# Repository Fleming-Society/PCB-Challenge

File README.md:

# UCL Fleming x KCL Tech x Oxford Engineering: 2026 PCB Challenge | Sponsored by PCBWay

UCL, KCL and Oxford are proud to present the 2026 PCB Challenge. Many thanks to PCBWay for sponsoring the prizes. 

If you have any questions please email zceepvb@ucl.ac.uk. Please keep in mind you cannot make a submission/be eligible for the prizes if you do not attend any of the universities organising this event. Within the 7 day period this event is being hosted, any university Engineering society is free to reach out to collaborate at this email address. 

All files are meant for KiCAD v10.0, if you have not updated, you probably should. It is a much better version than KiCAD v9.0 (includes dark mode). 

## Overview

This challenge invites participants to implement the given schematic as a fully wired PCB in the smallest possible size. As an added challenge the purpose of the PCB itself is left ambiguous. You are provided a schematic with all component values and connections intact, and a footprint associated with each schematic symbol. The event runs fully online, and all the necessary information can be found in this GitHub. 

I was inspired to create this challenge by a friend, Taylan Arslan, who gave me what was an essentially impossible challenge to get his PCB to fit within a 40mmx40mm constraint. Despite it being impossible, I learned a lot in those two days trying to accomplish this and the end result is a PCB that I am still very proud of. I hope that participants will also share the same feeling of satisfaction that I got, with the added bonus that this one is not impossible since the smallest possible size is to be determined by one of you. 

From my own experience, no matter how much you may like designing PCBs, ultimately it will become a bit repetitive. Thus to make this challenge more interesting; besides the monetary prize; I also decided to make the purpose of the PCB itself a puzzle to be solved.

## The Challenge

1. **Logic Deduction**: deduce the digital logic function implemented by the provided schematic, purely from the schematic itself (no functional description is given). Deducing this will give you bonus points.
2. **PCB Layout**: design a fully wired, single board PCB implementation of that logic, optimised for the smallest possible board area, within the design constraints below.

This challenge will be running for 7 days, **until the midnight of October 19th.**

Make your **submission** here:
https://forms.cloud.microsoft/e/69LKd5ykra

Your challenge submission should be a public GitHub repo. In this repo you just need to include the files we need. Your submission for the logic deduction is in the form itself. 

## Design Constraints

The keep out zone of the ESP32 antenna does not have to cover any PCB area, it can be left hanging off the edge of the PCB. 

### Board & Layer Stack
- Four layer board (F.Cu / B.Cu + 2 inner layers), 1.6 mm standard FR4 thickness.
- Board outline may be any shape, but must be a single contiguous board (no panelisation or multi-board tricks to reduce measured area).
- Management of the 4 layer stack up (e.g. assignment of signal/power/ground to inner layers) is left entirely to the participant; there is no required or predefined ground/power/signal layer assignment. However, you will be penalised for a stack up that would not actually work. 

### Trace & Clearance Rules
- Minimum trace width: 0.15 mm (6 mil).
- Minimum clearance (trace to trace, trace to pad, trace to via): 0.15 mm (6 mil).
- Minimum copper to board edge clearance: 0.3 mm.
- These values should be set as the global minimum in KiCad's Clearance rules so DRC enforces them automatically. We will check the DRC ourselves when judging. 

### Via Rules
- Minimum via drill diameter: 0.3 mm.
- Minimum via annular ring: 0.15 mm (i.e. minimum via pad diameter of approximately 0.6 mm).
- Vias in pads are not permitted.

### Footprint Rules
- Only default KiCad footprints, or footprints explicitly provided as part of the challenge, may be used.
- Footprints must not be modified from the library originals (this will be checked via KiCad's "footprint does not match library" DRC warning; note that editing a local copy of the library will not bypass this check, and manual review may also be used).
- All footprints must have correctly defined courtyard layers (F.CrtYd / B.CrtYd), and courtyards must not overlap between components. This is enforced via KiCad's built in "courtyard overlap" DRC check.
- Traces and vias may not be routed underneath IC footprints (i.e. within the courtyard area of any IC).

### Silkscreen
- Boards do not need to retain fully legible silkscreen labelling. 

### DRC Pass Criteria
- All submitted boards must pass KiCad's Design Rule Checker (Inspect → Design Rules Checker) with **zero unresolved DRC errors**.
- DRC **warnings** (e.g. minor silkscreen clipping) will not disqualify a board, but excessive or careless warnings may count against a board at the routing quality tie break stage.
- A board with unresolved DRC errors is disqualified from the size based ranking regardless of its footprint area.

### Note on High-Speed & Power Rules
The challenge schematic does include a high speed signal paths (a differential pair requiring a continuous reference plane). It does not however have a significant power delivery requirement (e.g. wide power traces, stitching vias). As such, no specific power plane rules are imposed in this iteration. 

## Judging Criteria

1. **Pass/fail gate**: correct logic deduction and a fully wired, DRC clean board (zero errors) under the given constraints. Boards failing either condition are not eligible for prizes.
2. **Primary ranking metric**: smallest board area (bounding box of the board outline), among all boards that pass the gate above.
3. **Tie breaker**: in the event of a tie, judges will assess routing quality and general layout practice (e.g. via count, trace directness, use of ground fill, silkscreen space, DRC warning count) to determine placement.

## Prizes

- **1st place:** £200
- **2nd place:** £100
- **3rd place:** £50

- All participants who submit a valid entry will receive a certificate of participation, a 10$ coupon on orders above 30$ for PCBWay and a PCB ruler from PCBWay. To be classified as a participant you must actually complete the PCB, this meaning that all the connections have been connected with a trace. Auto trace does not count. 

Expect the results to be announced within a week or two from the end date of the challenge.

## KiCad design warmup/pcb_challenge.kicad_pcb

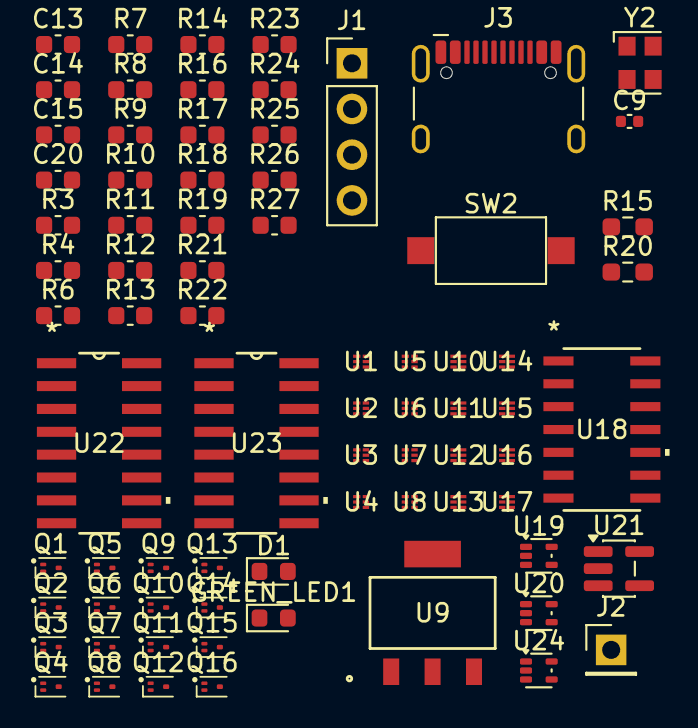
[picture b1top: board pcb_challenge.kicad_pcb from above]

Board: 2 copper layers, 76 parts (0 on the bottom side), 44 nets, no tracks yet.

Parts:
C9: 100nF; C_0402_1005Metric
C13, C14: 1uF; C_0603_1608Metric
C15, C20: 10uF; C_0603_1608Metric
D1: BLED; LED_0603_1608Metric
GREEN_LED1: LED; LED_0603_1608Metric
J1: Conn_01x04_Pin; PinHeader_1x04_P2.54mm_Vertical
J2: Conn_01x01_Pin; PinHeader_1x01_P2.54mm_Vertical
J3: USB_C_Receptacle_HCTL_HC-TYPE-C-16P-01A
Q1, Q2, Q3, Q4, Q5, Q6, Q7, Q8, Q9, Q10, Q11, Q12, Q13, Q14, Q15, Q16: Q_Dual_NPN_PNP_B1E2B2C2E1C1; SOT-1123
R3: 1k; C_0603_1608Metric
R4: 330; C_0603_1608Metric
R6, R24: 1M; C_0603_1608Metric
R7, R8, R9, R10, R11, R12, R13, R14, R16, R17, R18, R19, R21, R22, R23, R25, R26, R27: 10k; C_0603_1608Metric
R15, R20: 5.1k; R_0603_1608Metric_Pad0.98x0.95mm_HandSolder
SW2: SW_MEC_5G; SW_SPST_CK_RS282G05A3
U1, U2, U3, U4, U5, U6, U7, U8, U10, U11, U12, U13, U14, U15, U16, U17: 74AUP1G80; XSON6_SOT1115_NEX
U9: TC1262-25; SOT-223_3MC_MCH
U18: 4068; D14-L
U19, U20, U24: 74LVC1GU04DRL; SOT-553
U21: 74LV1T08GV; SC-74A-5_1.55x2.9mm_P0.95mm
U22, U23: CD74HC283M96; D16
Y2: KC2520Z; Oscillator_SMD_Kyocera_KC2520Z-4Pin_2.5x2.0mm

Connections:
+3.3V: C14.1, R3.1, U1.5 (VCC), U2.5 (VCC), U3.5 (VCC), U4.5 (VCC), U5.5 (VCC), U6.5 (VCC), U7.5 (VCC), U8.5 (VCC), U9.3 (VO), U10.5 (VCC), U11.5 (VCC), U12.5 (VCC), U13.5 (VCC), U14.5 (VCC), U15.5 (VCC), U16.5 (VCC), U17.5 (VCC), U18.14 (Vdd), U19.5 (VCC), U20.5 (VCC), U21.5 (VCC), U22.16 (VCC), U23.16 (VCC), U24.5 (VCC), Y2.4 (VCC)
+5V: C13.1, C15.1, C20.1, GREEN_LED1.2 (A), J3.A4 (VBUS), J3.A9 (VBUS), J3.B4 (VBUS), J3.B9 (VBUS), U9.1 (VI)
CLK: R7.2, U1.2 (C), U2.2 (C), U3.2 (C), U4.2 (C), U5.2 (C), U6.2 (C), U7.2 (C), U8.2 (C), U10.2 (C), U11.2 (C), U12.2 (C), U13.2 (C), U14.2 (C), U15.2 (C), U16.2 (C), U17.2 (C), Y2.3 (CLK)
COUT: U22.9 (COUT), U23.7 (CIN)
D0: U10.4 (~Q), U11.1 (D), U22.6 (B0)
D1: U11.4 (~Q), U12.1 (D), U22.2 (B1)
D2: U12.4 (~Q), U13.1 (D), U22.15 (B2)
D3: U13.4 (~Q), U14.1 (D), U22.11 (B3)
D4: U14.4 (~Q), U15.1 (D), U23.6 (B0)
D5: U15.4 (~Q), U16.1 (D), U23.2 (B1)
D6: U16.4 (~Q), U17.1 (D), U23.15 (B2)
D7: U17.4 (~Q), U23.11 (B3)
EN: J1.1, U21.1 (B), Y2.1 (INH)
F: J2.1 (Pin_1_1), U18.1 (K)
GND: C9.2, C13.2, C14.2, C15.2, C20.2, D1.1 (K), J3.A1 (GND), J3.A12 (GND), J3.B1 (GND), J3.B12 (GND), R4.1, R6.1, R7.1, R8.1, R9.1, R10.1, R11.1, R12.1, R13.1, R14.1, R15.1, R16.1, R17.1, R18.1, R19.1, R20.2, R21.1, R22.1, R23.1, R24.1, R25.1, R26.1, R27.1, SW2.1 (A), SW2.2 (A), U1.3 (GND), U2.3 (GND), U3.3 (GND), U4.3 (GND), U5.3 (GND), U6.3 (GND), U7.3 (GND), U8.3 (GND), U9.2 (GND), U10.3 (GND), U11.3 (GND), U12.3 (GND), U13.3 (GND), U14.3 (GND), U15.3 (GND), U16.3 (GND), U17.3 (GND), U18.7 (Vss), U19.3 (GND), U20.3 (GND), U21.3 (GND), U22.8 (GND), U23.8 (GND), U24.3 (GND), Y2.2 (GND)
Input 1: J1.4, U1.1 (D)
Input 2: J1.3, U10.1 (D)
unnamed: D1.2 (A), R3.2
unnamed: GREEN_LED1.1 (K), R4.2
unnamed: J3.A5 (CC1), R20.1
unnamed: J3.B5 (CC2), R15.2
unnamed: R6.2, R24.2
unnamed: R25.2, U22.7 (CIN)
Q0: U1.4 (~Q), U2.1 (D), U22.5 (A0)
Q1: U2.4 (~Q), U3.1 (D), U22.3 (A1)
Q2: U3.4 (~Q), U4.1 (D), U22.14 (A2)
Q3: U4.4 (~Q), U5.1 (D), U22.12 (A3)
Q4: U5.4 (~Q), U6.1 (D), U23.5 (A0)
Q5: U6.4 (~Q), U7.1 (D), U23.3 (A1)
Q6: U7.4 (~Q), U8.1 (D), U23.14 (A2)
Q7: U8.4 (~Q), U23.12 (A3)
RST: J1.2, U21.2 (A)
R_RST: Q1.1 (B1_1), Q2.1 (B1_1), Q3.1 (B1_1), Q4.1 (B1_1), Q5.1 (B1_1), Q6.1 (B1_1), Q7.1 (B1_1), Q8.1 (B1_1), Q9.1 (B1_1), Q10.1 (B1_1), Q11.1 (B1_1), Q12.1 (B1_1), Q13.1 (B1_1), Q14.1 (B1_1), Q15.1 (B1_1), Q16.1 (B1_1), R8.2, R9.2, R10.2, R11.2, R12.2, R13.2, R14.2, R16.2, R17.2, R18.2, R19.2, R21.2, R22.2, R23.2, R26.2, R27.2, U21.4 (Y)
S0: U19.2, U22.4 (S0)
S1: U18.3 (B), U22.1 (S1)
S2: U18.4 (C), U22.13 (S2)
S3: U22.10 (S3), U24.2
S4: U18.9 (E), U23.4 (S0)
S5: U18.10 (F), U23.1 (S1)
S6: U20.2, U23.13 (S2)
S7: U18.12 (H), U23.10 (S3)
T0: U18.2 (A), U19.4
T3: U18.5 (D), U24.4
T6: U18.11 (G), U20.4

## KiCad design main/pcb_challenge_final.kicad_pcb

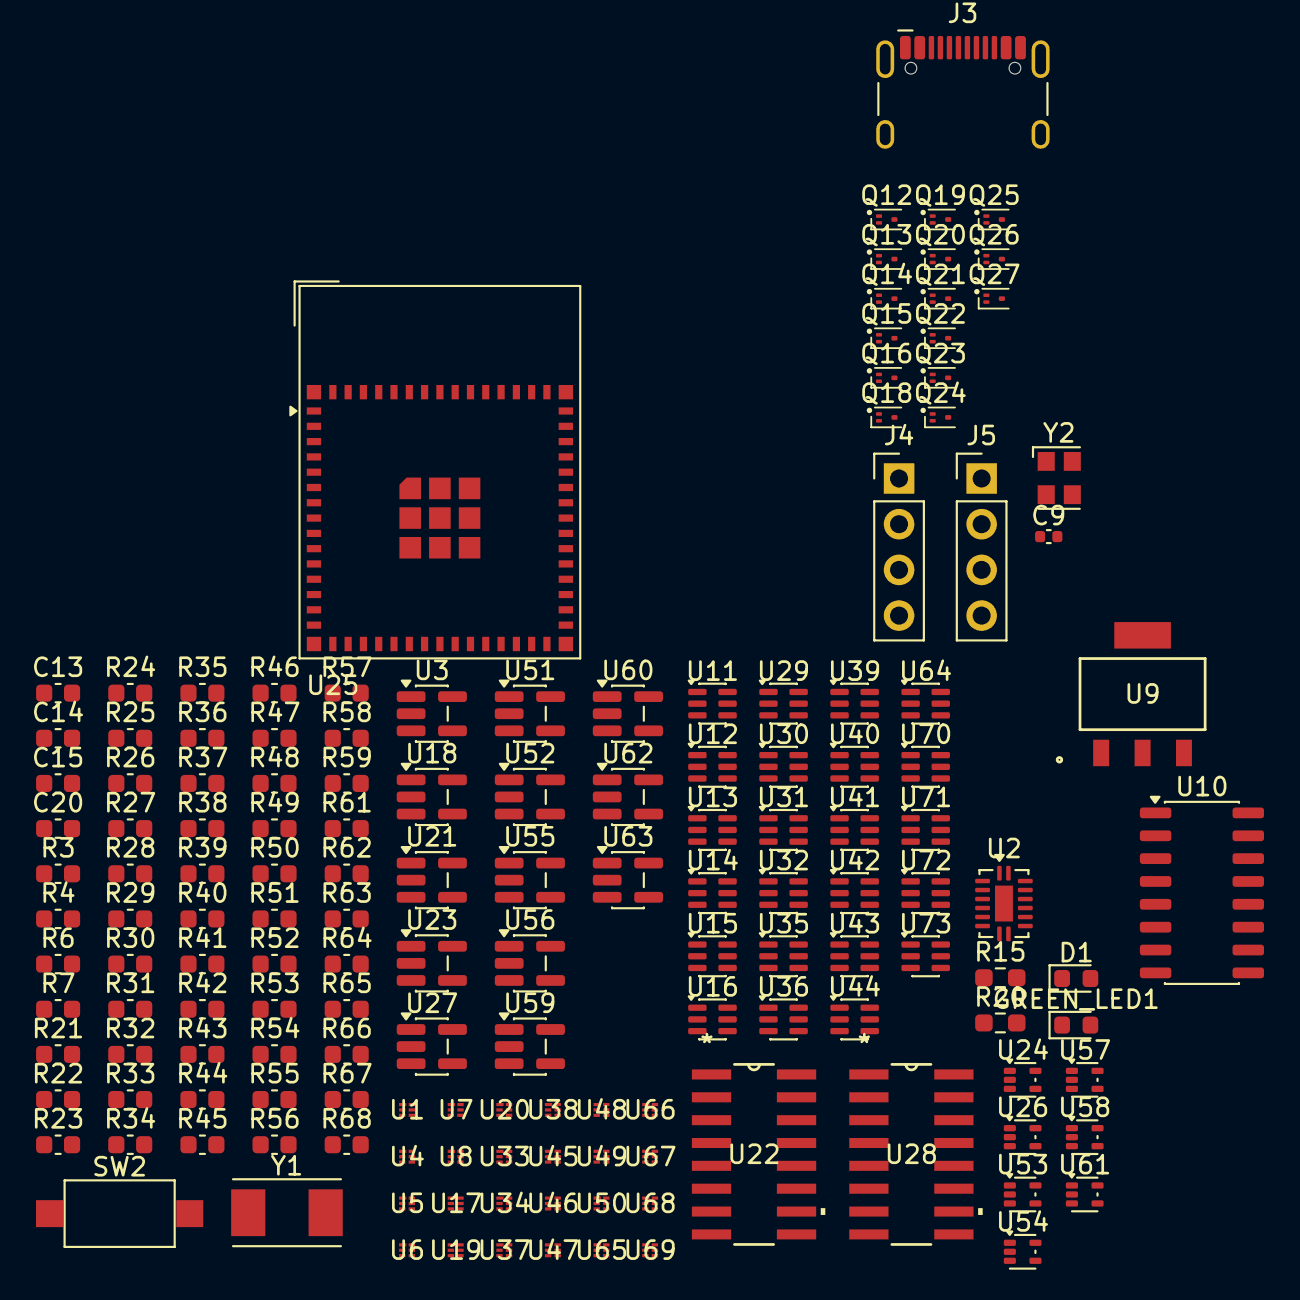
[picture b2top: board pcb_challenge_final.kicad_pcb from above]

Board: 2 copper layers, 154 parts (0 on the bottom side), 118 nets, no tracks yet.

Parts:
C9: 100nF; C_0402_1005Metric
C13, C14: 1uF; C_0603_1608Metric
C15, C20: 10uF; C_0603_1608Metric
D1: BLED; LED_0603_1608Metric
GREEN_LED1: LED; LED_0603_1608Metric
J3: USB_C_Receptacle_HCTL_HC-TYPE-C-16P-01A
J4, J5: Conn_01x04_Pin; PinHeader_1x04_P2.54mm_Vertical
Q12, Q13, Q14, Q15, Q16, Q18, Q19, Q20, Q21, Q22, Q23, Q24, Q25, Q26, Q27: Q_Dual_NPN_PNP_B1E2B2C2E1C1; SOT-1123
R3: 1k; C_0603_1608Metric
R4: 330; C_0603_1608Metric
R6, R24: 1M; C_0603_1608Metric
R7, R21, R22, R23, R25, R26, R27, R28, R29, R30, R31, R32, R33, R34, R35, R36, R37, R38, R39, R40, R41, R42, R43, R44, R45, R46, R47, R48, R49, R50, R51, R52, R53, R54, R55, R56, R57, R58, R59, R61, R62, R63, R64, R65, R66, R67, R68: 10k; C_0603_1608Metric
R15, R20: 5.1k; R_0603_1608Metric_Pad0.98x0.95mm_HandSolder
SW2: SW_MEC_5G; SW_SPST_CK_RS282G05A3
U1, U4, U5, U6, U7, U8, U17, U19, U20, U33, U34, U37, U38, U45, U46, U47, U48, U49, U50, U65, U66, U67, U68, U69: 74AUP1G80; XSON6_SOT1115_NEX
U2: NMUX1308BQ; DHVQFN-16-1EP_2.5x3.5mm_P0.5mm_EP1x2mm
U3, U18, U52, U55, U56, U60: 74AHC1G86; SC-74A-5_1.55x2.9mm_P0.95mm
U9: TC1262-25; SOT-223_3MC_MCH
U10: NMUX1308BQ; SO-16_3.9x9.9mm_P1.27mm
U11, U12, U13, U14, U15, U16, U29, U30, U31, U32, U35, U36, U39, U40, U41, U42, U43, U44, U64, U70, U71, U72, U73: NMUX1308BQ; SOT-363_SC-70-6
U21, U23, U27, U51, U59, U62, U63: 74LV1T08GV; SC-74A-5_1.55x2.9mm_P0.95mm
U22, U28: CD74HC283M96; D16
U24, U26, U53, U54, U57, U58, U61: 74LVC1GU04DRL; SOT-553
U25: ESP32-S3-MINI-1; ESP32-S2-MINI-1
Y1: 32.768KHz; Crystal_SMD_Abracon_ABM7-2Pin_6.0x3.5mm
Y2: KC2520Z; Oscillator_SMD_Kyocera_KC2520Z-4Pin_2.5x2.0mm

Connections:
+3.3V: C14.1, R3.1, U1.5 (VCC), U3.5 (VCC), U4.5 (VCC), U5.5 (VCC), U6.5 (VCC), U7.5 (VCC), U8.5 (VCC), U9.3 (VO), U10.1 (V_{CC}), U11.2 (V_{CC}), U12.2 (V_{CC}), U13.2 (V_{CC}), U14.2 (V_{CC}), U15.2 (V_{CC}), U16.2 (V_{CC}), U17.5 (VCC), U18.5 (VCC), U19.5 (VCC), U20.5 (VCC), U21.5 (VCC), U22.6 (B0), U22.16 (VCC), U23.5 (VCC), U24.5 (+), U26.5 (+), U27.5 (VCC), U28.6 (B0), U28.16 (VCC), U29.2 (V_{CC}), U30.2 (V_{CC}), U31.2 (V_{CC}), U32.2 (V_{CC}), U33.5 (VCC), U34.5 (VCC), U35.2 (V_{CC}), U36.2 (V_{CC}), U37.5 (VCC), U38.5 (VCC), U39.2 (V_{CC}), U40.2 (V_{CC}), U41.2 (V_{CC}), U42.2 (V_{CC}), U43.2 (V_{CC}), U44.2 (V_{CC}), U45.5 (VCC), U46.5 (VCC), U47.5 (VCC), U48.5 (VCC), U49.5 (VCC), U50.5 (VCC), U51.5 (VCC), U52.5 (VCC), U53.5 (+), U54.5 (+), U55.5 (VCC), U56.5 (VCC), U57.5 (+), U58.5 (+), U59.5 (VCC), U60.5 (VCC), U61.5 (+), U62.5 (VCC), U63.5 (VCC), U64.2 (V_{CC}), U64.6 (Y1), U65.5 (VCC), U66.5 (VCC), U67.5 (VCC), U68.5 (VCC), U69.5 (VCC), U70.2 (V_{CC}), U71.2 (V_{CC}), U72.2 (V_{CC}), U73.2 (V_{CC}), Y2.4 (VCC)
+5V: C13.1, C15.1, C20.1, GREEN_LED1.2 (A), J3.A4 (VBUS), J3.A9 (VBUS), J3.B4 (VBUS), J3.B9 (VBUS), U9.1 (VI)
???: J5.4, U1.4 (~Q), U26.2
CLK: R7.2, Y2.3 (CLK)
COUT: U22.9 (COUT), U28.9 (COUT)
GND: C9.2, C13.2, C14.2, C15.2, C20.2, D1.1 (K), J3.A1 (GND), J3.A12 (GND), J3.B1 (GND), J3.B12 (GND), R4.1, R6.1, R7.1, R15.1, R20.2, R21.1, R22.1, R23.1, R24.1, R25.1, R26.1, R27.1, R28.1, R29.1, R30.1, R31.1, R32.1, R33.1, R34.1, R35.1, R36.1, R37.1, R38.1, R39.1, R40.1, R41.1, R42.1, R43.1, R44.1, R45.1, R46.1, R47.1, R48.1, R49.1, R50.1, R51.1, R52.1, R53.1, R54.1, R55.1, R56.1, R57.1, R58.1, R59.1, R61.1, R62.1, R63.1, R64.1, R65.1, R66.1, R67.1, R68.1, SW2.1 (A), SW2.2 (A), U1.3 (GND), U3.3 (GND), U4.3 (GND), U5.3 (GND), U6.3 (GND), U7.3 (GND), U8.3 (GND), U9.2 (GND), U10.2 (GND), U11.3 (GND), U12.3 (GND), U13.3 (GND), U14.3 (GND), U15.3 (GND), U16.3 (GND), U17.3 (GND), U18.3 (GND), U19.3 (GND), U20.3 (GND), U21.3 (GND), U22.8 (GND), U23.3 (GND), U24.3 (-), U25.1 (GND), U26.3 (-), U27.3 (GND), U28.8 (GND), U29.3 (GND), U30.3 (GND), U31.3 (GND), U32.3 (GND), U33.3 (GND), U34.3 (GND), U35.3 (GND), U36.3 (GND), U37.3 (GND), U38.3 (GND), U39.3 (GND), U40.3 (GND), U41.3 (GND), U42.3 (GND), U43.3 (GND), U44.3 (GND), U45.3 (GND), U46.3 (GND), U47.3 (GND), U48.3 (GND), U49.3 (GND), U50.3 (GND), U51.3 (GND), U52.3 (GND), U53.3 (-), U54.3 (-), U55.3 (GND), U56.3 (GND), U57.3 (-), U58.3 (-), U59.3 (GND), U60.3 (GND), U61.3 (-), U62.3 (GND), U63.3 (GND), U64.3 (GND), U65.3 (GND), U66.3 (GND), U67.3 (GND), U68.3 (GND), U69.3 (GND), U70.3 (GND), U71.3 (GND), U72.3 (GND), U73.3 (GND), Y2.2 (GND)
IO6: U6.2 (C), U7.2 (C), U8.2 (C), U25.10 (IO6), U45.2 (C), U46.2 (C), U47.2 (C), U48.2 (C), U49.2 (C), U50.2 (C), U65.2 (C), U66.2 (C), U67.2 (C), U68.2 (C), U69.2 (C)
IO7: U21.2 (A), U25.11 (IO7)
IO8: Q18.1 (B1_1), Q19.1 (B1_1), Q20.1 (B1_1), Q24.1 (B1_1), Q25.1 (B1_1), Q26.1 (B1_1), Q27.1 (B1_1), R35.2, R37.2, R39.2, R61.2, R63.2, R65.2, R67.2, U25.12 (IO8), U39.1 (S0), U40.1 (S0), U41.1 (S0), U42.1 (S0), U43.1 (S0), U44.1 (S0), U64.1 (S0)
IO9: U24.2, U25.13 (IO9), U65.4 (~Q)
IO10: U25.14 (IO10), U69.4 (~Q), U73.5 (Y0)
IO11: U25.15 (IO11), U68.4 (~Q), U70.5 (Y0)
IO12: U25.16 (IO12), U67.4 (~Q), U71.5 (Y0)
IO13: U25.17 (IO13), U66.4 (~Q), U72.5 (Y0)
unnamed: D1.2 (A), R3.2
unnamed: GREEN_LED1.1 (K), R4.2
unnamed: J3.A5 (CC1), R20.1
unnamed: J3.B5 (CC2), R15.2
unnamed: R6.2, R24.2
unnamed: U1.1 (D), U27.4 (Y)
unnamed: U66.1 (D), U72.4 (Out)
unnamed: U67.1 (D), U71.4 (Out)
unnamed: U68.1 (D), U70.4 (Out)
unnamed: U69.1 (D), U73.4 (Out)
unnamed: U18.4, U54.2
unnamed: U21.1 (B), U24.4
unnamed: R33.2, U22.2 (B1), U22.11 (B3), U22.12 (A3), U22.15 (B2)
unnamed: R25.2, U22.7 (CIN)
unnamed: U23.1 (B), U26.4
unnamed: U25.2 (GND), U25.42 (GND), U25.43 (GND), U25.46 (GND), U25.47 (GND), U25.48 (GND), U25.49 (GND), U25.50 (GND), U25.51 (GND), U25.52 (GND), U25.53 (GND), U25.54 (GND), U25.55 (GND), U25.56 (GND), U25.57 (GND), U25.58 (GND), U25.59 (GND), U25.60 (GND), U25.61 (GND), U25.62 (GND), U25.63 (GND), U25.64 (GND), U25.65 (GND)
unnamed: U25.19 (IO15), Y1.2
unnamed: U25.20 (IO16), Y1.1
unnamed: U3.4, U27.2 (A)
unnamed: U27.1 (B), U51.4 (Y)
unnamed: R47.2, U28.2 (B1), U28.11 (B3), U28.12 (A3), U28.15 (B2)
unnamed: R34.2, U28.7 (CIN)
unnamed: U4.1 (D), U29.4 (Out)
unnamed: R48.2, U29.6 (Y1)
unnamed: U5.1 (D), U30.4 (Out)
unnamed: U4.4 (~Q), U30.5 (Y0)
unnamed: R49.2, U30.6 (Y1)
unnamed: U31.4 (Out), U33.1 (D)
unnamed: R50.2, U31.6 (Y1)
unnamed: U32.4 (Out), U34.1 (D)
unnamed: U32.5 (Y0), U33.4 (~Q)
unnamed: R51.2, U32.6 (Y1)
unnamed: U35.4 (Out), U37.1 (D)
unnamed: R52.2, U35.6 (Y1)
unnamed: U36.4 (Out), U38.1 (D)
unnamed: U36.5 (Y0), U37.4 (~Q)
unnamed: R53.2, U36.6 (Y1)
unnamed: U39.4 (Out), U45.1 (D)
unnamed: R54.2, U39.6 (Y1)
unnamed: U40.4 (Out), U46.1 (D)
unnamed: R55.2, U40.6 (Y1)
unnamed: U41.4 (Out), U47.1 (D)
unnamed: R56.2, U41.6 (Y1)
unnamed: U42.4 (Out), U48.1 (D)
unnamed: U42.5 (Y0), U45.4 (~Q)
unnamed: R57.2, U42.6 (Y1)
unnamed: U43.4 (Out), U49.1 (D)
unnamed: U43.5 (Y0), U46.4 (~Q)
unnamed: R58.2, U43.6 (Y1)
unnamed: U44.4 (Out), U50.1 (D)
unnamed: U44.5 (Y0), U47.4 (~Q)
unnamed: R59.2, U44.6 (Y1)
unnamed: U51.2 (A), U54.4
unnamed: U51.1 (B), U53.4
unnamed: U52.4, U53.2
unnamed: U55.4, U57.2
unnamed: U56.4, U58.2
unnamed: U57.4, U59.2 (A)
unnamed: U58.4, U59.1 (B), U62.2 (A)
unnamed: U59.4 (Y), U63.2 (A)
unnamed: U60.4, U61.2
unnamed: U61.4, U62.1 (B)
unnamed: U62.4 (Y), U63.1 (B)
unnamed: U63.4 (Y), U64.5 (Y0)
unnamed: U64.4 (Out), U65.1 (D)
R_en: U10.12 (EN), U14.1 (S0), U15.1 (S0), U16.1 (S0), U23.4 (Y)
USB_D+: J3.A6 (D+), J3.B6 (D+), U25.24 (USB_D+)
USB_D-: J3.A7 (D-), J3.B7 (D-), U25.23 (USB_D-)
b1: J4.4, U10.4 (in1)
b2: J4.3, U10.5 (in2)
b3: J4.2, U10.6 (in3)
b4: J4.1, U10.7 (in4)
clk: J5.3, U1.2 (C), U4.2 (C), U5.2 (C), U10.3 (clk), U17.2 (C), U19.2 (C), U20.2 (C), U33.2 (C), U34.2 (C), U37.2 (C), U38.2 (C)
en: J5.1, U23.2 (A)
out_1: U10.13 (o1), U73.6 (Y1)
out_2: U10.14 (o2), U70.6 (Y1)
out_3: U10.15 (o3), U71.6 (Y1)
out_4: U10.16 (o4), U72.6 (Y1)
r_en: U11.1 (S0), U12.1 (S0), U13.1 (S0), U21.4 (Y), U70.1 (S0), U71.1 (S0), U72.1 (S0), U73.1 (S0)
rc1: U7.4 (~Q), U10.10 (in1), U12.5 (Y0), U22.5 (A0), U60.1
rc2: U6.4 (~Q), U10.11 (in2), U11.5 (Y0), U22.3 (A1), U56.2
rc3: U8.4 (~Q), U13.5 (Y0), U22.14 (A2), U55.2
reg1: U5.4 (~Q), U18.1
reg2: U34.4 (~Q), U52.1
reg3: U3.1, U38.4 (~Q)
rs0: U12.6 (Y1), U22.4 (S0)
rs1: U11.6 (Y1), U22.1 (S1)
rs2: U13.6 (Y1), U22.13 (S2)
rst: J5.2, Q12.1 (B1_1), Q13.1 (B1_1), Q14.1 (B1_1), Q15.1 (B1_1), Q16.1 (B1_1), Q21.1 (B1_1), Q22.1 (B1_1), Q23.1 (B1_1), R21.2, R23.2, R27.2, R29.2, R31.2, R41.2, R42.2, R43.2, U29.1 (S0), U30.1 (S0), U31.1 (S0), U32.1 (S0), U35.1 (S0), U36.1 (S0)
rw1: U7.1 (D), U12.4 (Out), U29.5 (Y0)
rw2: U6.1 (D), U11.4 (Out), U31.5 (Y0)
rw3: U8.1 (D), U13.4 (Out), U35.5 (Y0)
wc1: U10.8 (in1), U15.5 (Y0), U18.2, U20.4 (~Q), U28.5 (A0)
wc2: U10.9 (in2), U14.5 (Y0), U19.4 (~Q), U28.3 (A1), U52.2
wc3: U3.2, U16.5 (Y0), U17.4 (~Q), U28.14 (A2)
wir1: U48.4 (~Q), U60.2
wir2: U49.4 (~Q), U56.1
wir3: U50.4 (~Q), U55.1
wr1: U15.4 (Out), U20.1 (D), U39.5 (Y0)
wr2: U14.4 (Out), U19.1 (D), U40.5 (Y0)
wr3: U16.4 (Out), U17.1 (D), U41.5 (Y0)
ws0: U15.6 (Y1), U28.4 (S0)
ws1: U14.6 (Y1), U28.1 (S1)
ws2: U16.6 (Y1), U28.13 (S2)
